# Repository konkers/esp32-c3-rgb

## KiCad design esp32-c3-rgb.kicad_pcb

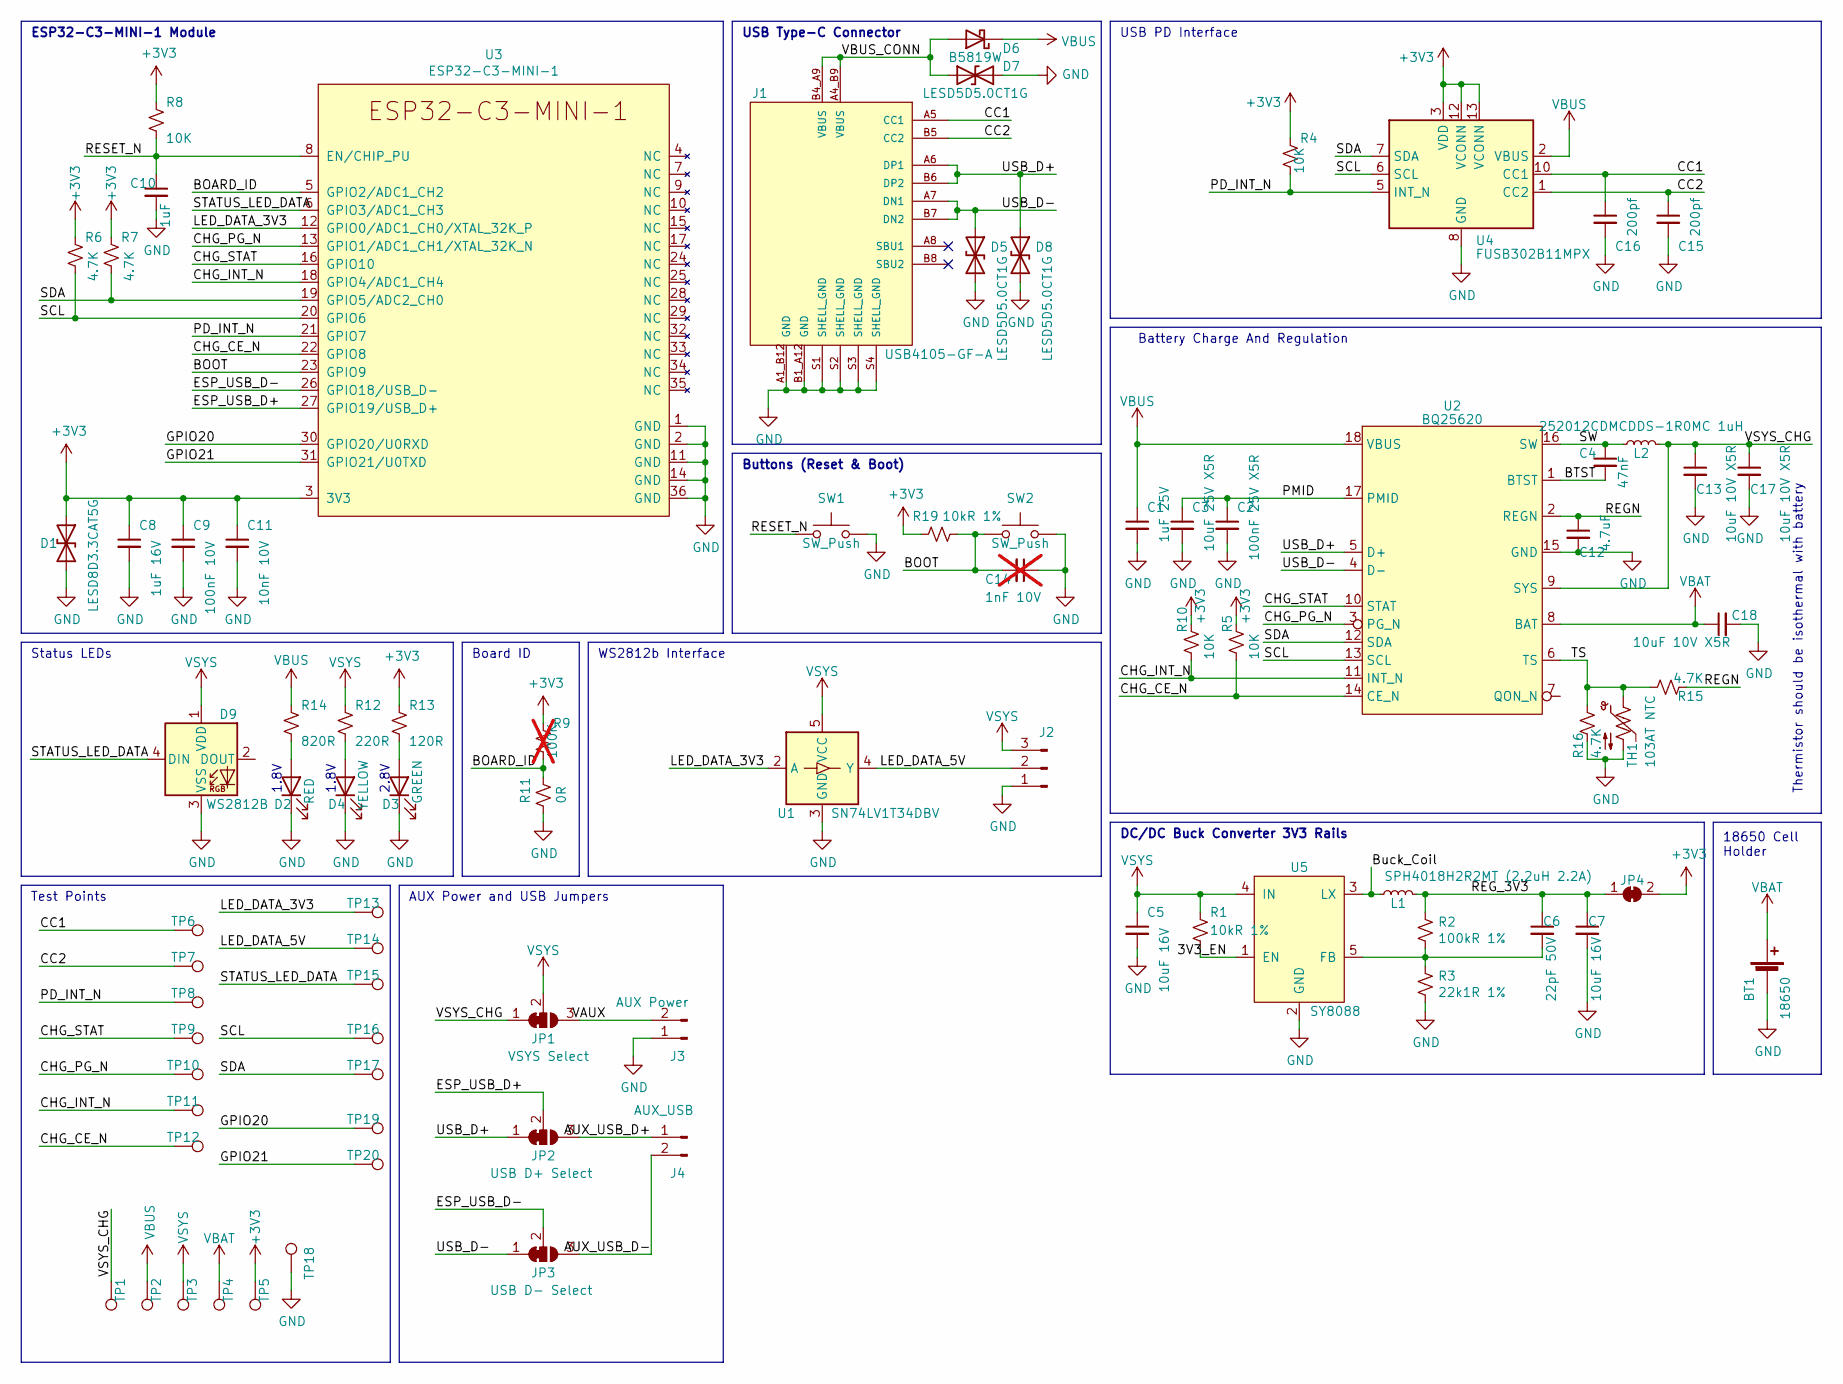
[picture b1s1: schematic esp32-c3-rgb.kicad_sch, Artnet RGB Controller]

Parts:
BT1: 18650; BatteryHolder_Keystone_1042_1x18650
C1: 1uF 25V; C_0402_1005Metric; LCSC C52923
C2: 100nF 25V X5R; C_0402_1005Metric; LCSC C1525
C3: 10uF 25V X5R; C_0603_1608Metric; LCSC C15195
C4: 47nF; C_0402_1005Metric; LCSC C1525
C5, C7: 10uF 16V; C_0805_2012Metric; LCSC C15850
C6: 22pF 50V; C_0603_1608Metric; LCSC C1653
C8: 1uF 16V; C_0402_1005Metric; LCSC C52923
C9: 100nF 10V; C_0402_1005Metric; LCSC C1525
C10: 1uF; C_0402_1005Metric; LCSC C52923
C11: 10nF 10V; C_0402_1005Metric; LCSC C15195
C12: 4.7uF; C_0402_1005Metric; LCSC C1525
C13, C17, C18: 10uF 10V X5R; C_0603_1608Metric; LCSC C1525
C14: 1nF 10V; C_0402_1005Metric; LCSC C1523; not fitted
C15, C16: 200pf; C_0402_1005Metric; LCSC C52923
D1: LESD8D3.3CAT5G; SOD-882; LCSC C172409
D2: RED; LED_0603_1608Metric_Pad1.05x0.95mm_HandSolder
D3: GREEN; LED_0603_1608Metric_Pad1.05x0.95mm_HandSolder
D4: YELLOW; LED_0603_1608Metric_Pad1.05x0.95mm_HandSolder
D5, D7, D8: LESD5D5.0CT1G; D_SOD-523; LCSC C383211
D6: B5819W; D_SOD-123; LCSC C8598
D9: WS2812B; LED_WS2812B_PLCC4_5.0x5.0mm_P3.2mm
J1: USB4105-GF-A; GCT_USB4105-GF-A; PARTREV A3; LCSC C165948
J2: Conn_01x03_Pin; PinHeader_1x03_P2.54mm_Vertical
J3: AUX Power; PinHeader_1x02_P2.54mm_Vertical
J4: AUX_USB; PinHeader_1x02_P2.54mm_Vertical
JP1: VSYS Select; SolderJumper-3_P1.3mm_Bridged12_RoundedPad1.0x1.5mm
JP2: USB D+ Select; SolderJumper-3_P1.3mm_Bridged12_RoundedPad1.0x1.5mm
JP3: USB D- Select; SolderJumper-3_P1.3mm_Bridged12_RoundedPad1.0x1.5mm
JP4: SolderJumper_2_Bridged; SolderJumper-2_P1.3mm_Bridged2Bar_RoundedPad1.0x1.5mm
L1: SPH4018H2R2MT (2.2uH 2.2A); L_Bourns-SRN4018; LCSC C370436
L2: 252012CDMCDDS-1R0MC 1uH; sumida_2.7x1.2; LCSC C370436
R1, R19: 10kR 1%; R_0402_1005Metric; LCSC C25744
R2: 100kR 1%; R_0402_1005Metric; LCSC C25741
R3: 22k1R 1%; R_0402_1005Metric; LCSC C43473
R4, R5, R8, R10: 10K; R_0402_1005Metric; LCSC C25744
R6, R7, R15, R16: 4.7K; R_0402_1005Metric; LCSC C25744
R9: 100K; R_0402_1005Metric; LCSC C25744; not fitted
R11: 0R; R_0402_1005Metric; LCSC C25744
R12: 220R; R_0402_1005Metric; LCSC C25744
R13: 120R; R_0402_1005Metric; LCSC C25744
R14: 820R; R_0402_1005Metric; LCSC C25744
SW1, SW2: SW_Push; SW_SPST_PTS810; LCSC C116501
TH1: 103AT NTC; PinHeader_1x02_P2.54mm_Vertical
TP1: VSYS_CHG; TestPoint_Loop_D2.60mm_Drill0.9mm_Beaded
TP2: VBUS; TestPoint_Loop_D2.60mm_Drill0.9mm_Beaded
TP3: VSYS; TestPoint_Pad_D1.0mm
TP4: VBAT; TestPoint_Loop_D2.60mm_Drill0.9mm_Beaded
TP5: 3V3; TestPoint_Loop_D2.60mm_Drill0.9mm_Beaded
TP6: CC1; TestPoint_Pad_D1.0mm
TP7: CC2; TestPoint_Pad_D1.0mm
TP8: PD_INT_N; TestPoint_Pad_D1.0mm
TP9: CHG_STAT; TestPoint_Pad_D1.0mm
TP10: CHG_PG_N; TestPoint_Pad_D1.0mm
TP11: CHG_INT_N; TestPoint_Pad_D1.0mm
TP12: CHG_CE_N; TestPoint_Pad_D1.0mm
TP13: LED_DATA_3V3; TestPoint_Pad_D1.0mm
TP14: LED_DATA_5V; TestPoint_Pad_D1.0mm
TP15: STATUS_LED_DATA; TestPoint_Pad_D1.0mm
TP16: SCL; TestPoint_Pad_D1.0mm
TP17: SDA; TestPoint_Pad_D1.0mm
TP18: GND; TestPoint_Loop_D2.60mm_Drill0.9mm_Beaded
TP19: GPIO0; TestPoint_Pad_D1.0mm
TP20: GPIO21; TestPoint_Pad_D1.0mm
U1: SN74LV1T34DBV; SOT-23-5
U2: BQ25620; BQ25620RYKR
U3: ESP32-C3-MINI-1; LCSC C2838502
U4: FUSB302B11MPX; WQFN-14-1EP_2.5x2.5mm_P0.5mm_EP1.45x1.45mm
U5: SY8088; SOT-23-5; LCSC C479072

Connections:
+3V3: C8.1, C9.1, C11.1, D1.1 (A1), JP4.2 (B), R4.1, R5.1, R6.1, R7.1, R8.1, R9.1, R10.1, R13.1, R19.1, TP5.1, U3.3 (3V3), U4.3 (VDD), U4.4 (VDD), U4.12 (VCONN), U4.13 (VCONN)
/3V3_EN: R1.2, U5.1 (EN)
/AUX_USB_D+: J4.1, JP2.3 (B)
/AUX_USB_D-: J4.2, JP3.3 (B)
/BOARD_ID: R9.2, R11.1, U3.5 (GPIO2/ADC1_CH2)
/BOOT: C14.2, R19.2, SW2.1, U3.23 (GPIO9)
/BTST: C4.2, U2.1 (BTST)
/Buck_Coil: L1.1, U5.3 (LX)
/CC1: C16.1, J1.A5 (CC1), TP6.1, U4.10 (CC1), U4.11 (CC1)
/CC2: C15.1, J1.B5 (CC2), TP7.1, U4.1 (CC2), U4.14 (CC2)
/CHG_CE_N: R5.2, TP12.1, U2.14 (CE_N), U3.22 (GPIO8)
/CHG_INT_N: R10.2, TP11.1, U2.11 (INT_N), U3.18 (GPIO4/ADC1_CH4)
/CHG_PG_N: TP10.1, U2.3 (PG_N), U3.13 (GPIO1/ADC1_CH1/XTAL_32K_N)
/CHG_STAT: TP9.1, U2.10 (STAT), U3.16 (GPIO10)
/ESP_USB_D+: JP2.2 (C), U3.27 (GPIO19/USB_D+)
/ESP_USB_D-: JP3.2 (C), U3.26 (GPIO18/USB_D-)
/GPIO20: TP19.1, U3.30 (GPIO20/U0RXD)
/GPIO21: TP20.1, U3.31 (GPIO21/U0TXD)
/LED_DATA_3V3: TP13.1, U1.2 (A), U3.12 (GPIO0/ADC1_CH0/XTAL_32K_P)
/LED_DATA_5V: J2.2, TP14.1, U1.4 (Y)
/PD_INT_N: R4.2, TP8.1, U3.21 (GPIO7), U4.5 (INT_N)
/PMID: C2.1, C3.1, U2.17 (PMID)
/REGN: C12.1, R15.2, U2.2 (REGN)
/REG_3V3: C6.1, C7.1, JP4.1 (A), L1.2, R2.1
/RESET_N: C10.1, R8.2, SW1.1, U3.8 (EN/CHIP_PU)
/SCL: R6.2, TP16.1, U2.13 (SCL), U3.20 (GPIO6), U4.6 (SCL)
/SDA: R7.2, TP17.1, U2.12 (SDA), U3.19 (GPIO5/ADC2_CH0), U4.7 (SDA)
/STATUS_LED_DATA: D9.4 (DIN), TP15.1, U3.6 (GPIO3/ADC1_CH3)
/SW: C4.1, L2.1, U2.16 (SW)
/TS: R15.1, R16.1, TH1.1, U2.6 (TS)
/USB_D+: D8.1 (A1), J1.A6 (DP1), J1.B6 (DP2), JP2.1 (A), U2.5 (D+)
/USB_D-: D5.1 (A1), J1.A7 (DN1), J1.B7 (DN2), JP3.1 (A), U2.4 (D-)
/VAUX: J3.2, JP1.3 (B)
/VBUS_CONN: D6.2 (A), D7.1 (A1), J1.A4_B9 (VBUS), J1.B4_A9 (VBUS)
/VSYS_CHG: C13.1, C17.1, JP1.1 (A), L2.2, TP1.1, U2.9 (SYS)
GND: BT1.2 (-), C1.2, C2.2, C3.2, C5.2, C7.2, C8.2, C9.2, C10.2, C11.2, C12.2, C13.2, C14.1, C15.2, C16.2, C17.2, C18.2, D1.2 (A2), D2.1 (K), D3.1 (K), D4.1 (K), D5.2 (A2), D7.2 (A2), D8.2 (A2), D9.3 (VSS), J1.A1_B12 (GND), J1.B1_A12 (GND), J1.S1 (SHELL_GND), J1.S2 (SHELL_GND), J1.S3 (SHELL_GND), J1.S4 (SHELL_GND), J2.1, J3.1, R3.2, R11.2, R16.2, SW1.2, SW2.2, TH1.2, TP18.1, U1.3 (GND), U2.15 (GND), U3.1 (GND), U3.2 (GND), U3.11 (GND), U3.14 (GND), U3.36 (GND), U4.8 (GND), U4.9 (GND), U4.15 (GND), U5.2 (GND)
unnamed: D2.2 (A), R14.2
unnamed: D3.2 (A), R13.2
unnamed: D4.2 (A), R12.2
unnamed: C6.2, R2.2, R3.1, U5.5 (FB)
VBAT: BT1.1 (+), C18.1, TP4.1, U2.8 (BAT)
VBUS: C1.1, D6.1 (K), R14.1, TP2.1, U2.18 (VBUS), U4.2 (VBUS)
VSYS: C5.1, D9.1 (VDD), J2.3, JP1.2 (C), R1.1, R12.1, TP3.1, U1.5 (VCC), U5.4 (IN)

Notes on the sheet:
AUX Power and USB Jumpers
Board ID
WS2812b Interface
2.8V
USB Type-C Connector
Buttons (Reset & Boot)
1.8V
USB PD Interface
Battery Charge And Regulation
DC/DC Buck Converter 3V3 Rails
Thermistor should be isothermal with battery
1.8V
Test Points
ESP32-C3-MINI-1 Module
Status LEDs
18650 Cell Holder

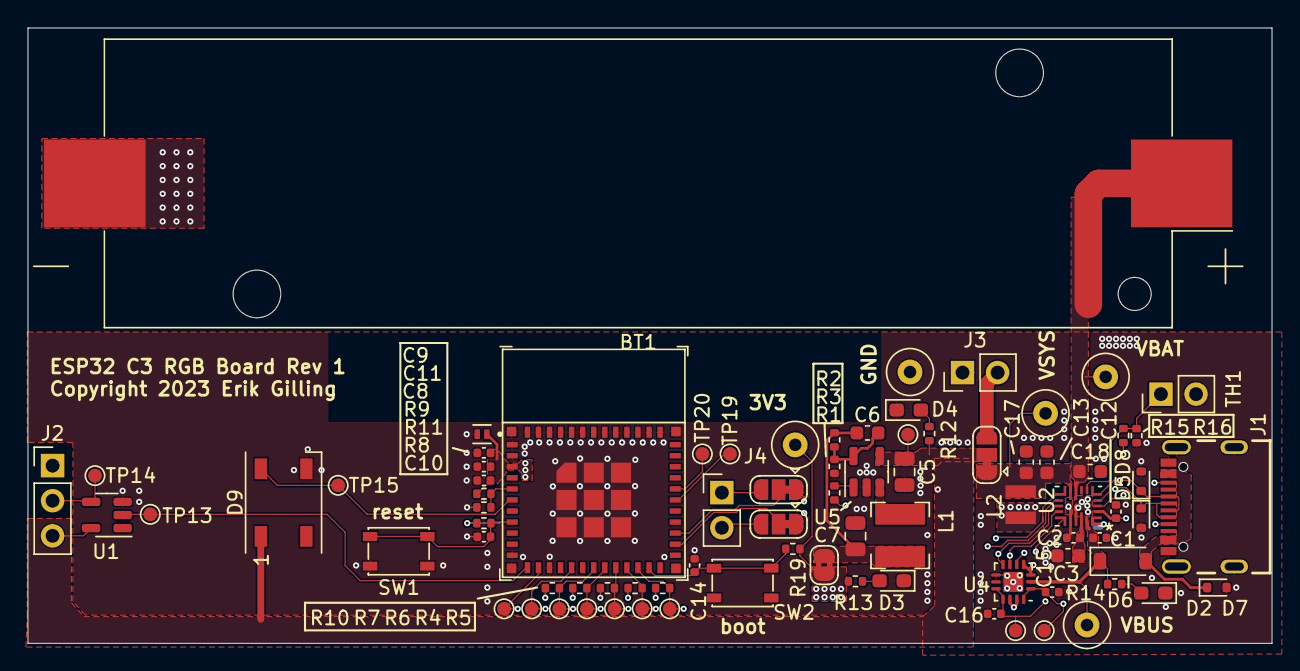
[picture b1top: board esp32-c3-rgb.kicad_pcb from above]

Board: 4 copper layers, 90.0 x 44.5 mm, 83 parts (1 on the bottom side), 43 nets.

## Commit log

2023-03-10 Rev1

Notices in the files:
esp32-c3-rgb.kicad_pcb:
Copyright 2023 Erik Gilling
parts and their libraries:
Copyright 2021 Accelerated Designs. All rights reserved.
